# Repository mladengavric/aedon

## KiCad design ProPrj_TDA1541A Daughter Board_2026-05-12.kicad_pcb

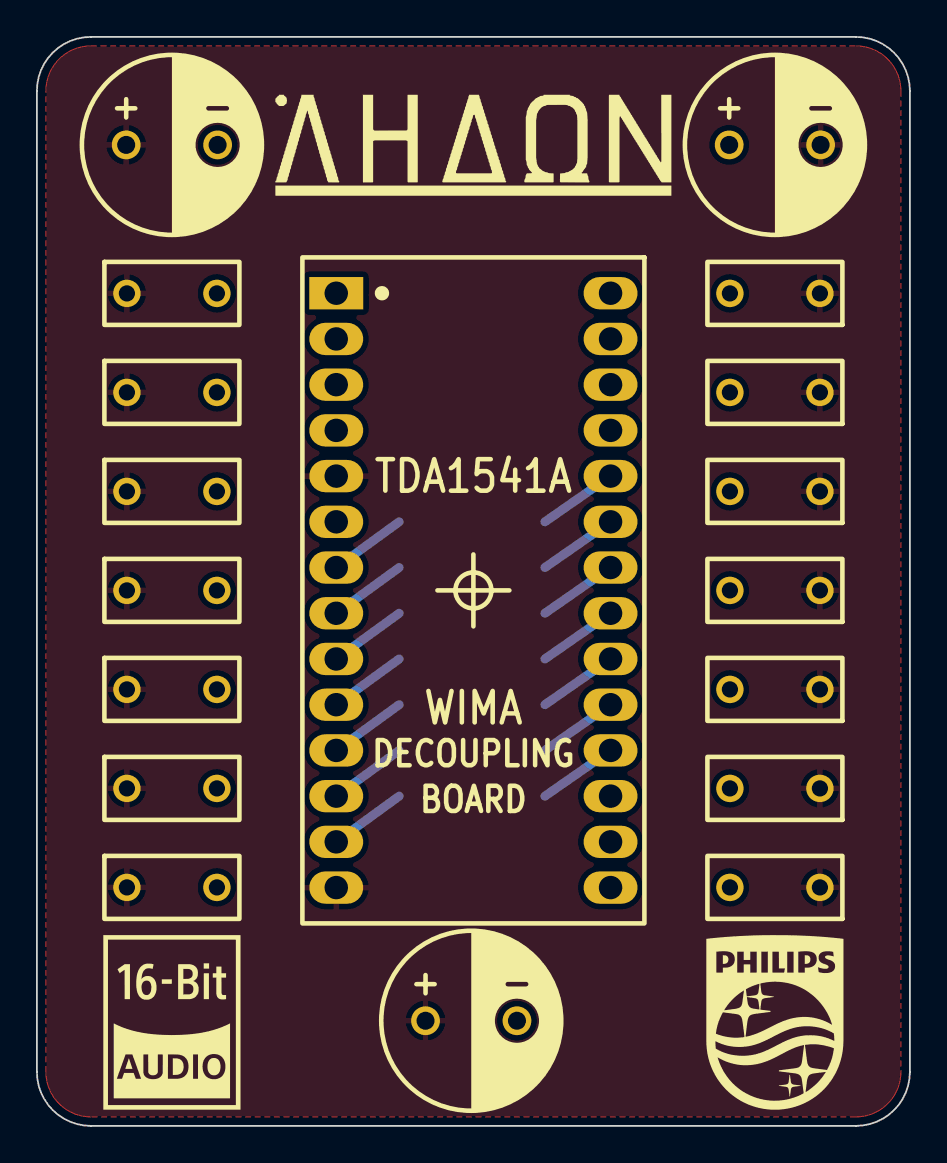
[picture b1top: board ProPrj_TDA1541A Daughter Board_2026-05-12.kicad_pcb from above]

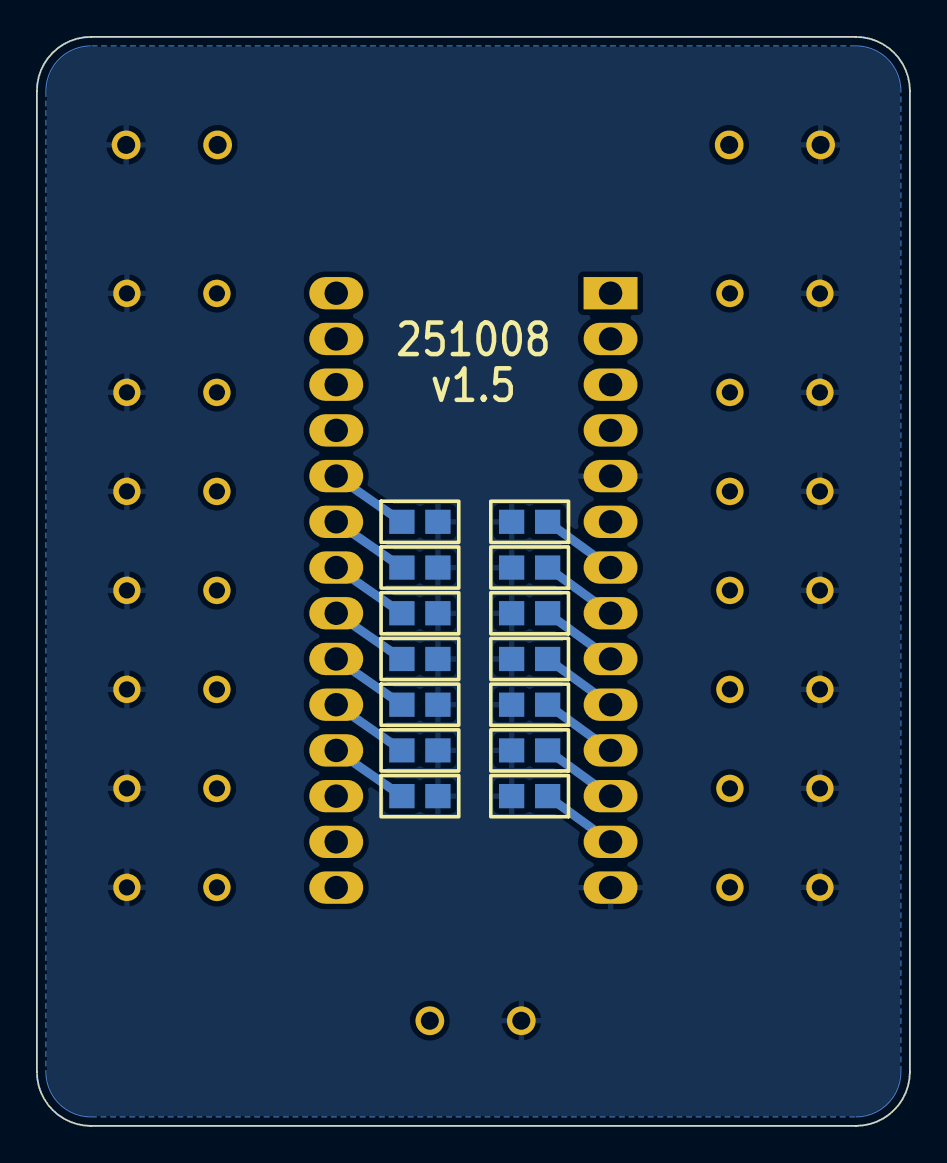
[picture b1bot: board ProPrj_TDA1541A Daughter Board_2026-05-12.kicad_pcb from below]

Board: 4 copper layers, 48.5 x 60.5 mm, 32 parts (14 on the bottom side), 18 nets.

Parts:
C1, C2, C3, C4, C5, C6, C7, C8, C9, C10, C11, C12, C13, C14: CAP-TH_L7.2-W3.5-P5.00-D0.5
C15, C16, C17, C18, C19, C20, C21, C22, C23, C24, C25, C26, C27, C28: C0805
C29, C30, C31: CAP-TH_BD10.0-P5.00-D1.0-FD
U1: 116-XX-628-41-003000

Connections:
$1N3486: C7.2, C21.1, U1.13
$1N3491: C6.2, C20.1, U1.12
$1N3497: C5.2, C19.1, U1.11
$1N3503: C4.2, C18.1, U1.10
$1N3509: C3.2, C17.1, U1.9
$1N3515: C2.2, C16.1, U1.8
$1N3521: C1.2, C15.1, U1.7
$1N3527: C8.2, C22.1, U1.18
$1N3533: C9.2, C23.1, U1.19
$1N3539: C10.2, C24.1, U1.20
$1N3545: C11.2, C25.1, U1.21
$1N3551: C12.2, C26.1, U1.22
$1N3557: C13.2, C27.1, U1.23
$1N3563: C14.2, C28.1, U1.24
$1N10314: C29.2, U1.15
$1N10391: C30.2, U1.26
$1N10468: C31.1, U1.28
GND: C1.1, C2.1, C3.1, C4.1, C5.1, C6.1, C7.1, C8.1, C9.1, C10.1, C11.1, C12.1, C13.1, C14.1, C15.2, C16.2, C17.2, C18.2, C19.2, C20.2, C21.2, C22.2, C23.2, C24.2, C25.2, C26.2, C27.2, C28.2, C29.1, C30.1, C31.2, U1.5, U1.14
